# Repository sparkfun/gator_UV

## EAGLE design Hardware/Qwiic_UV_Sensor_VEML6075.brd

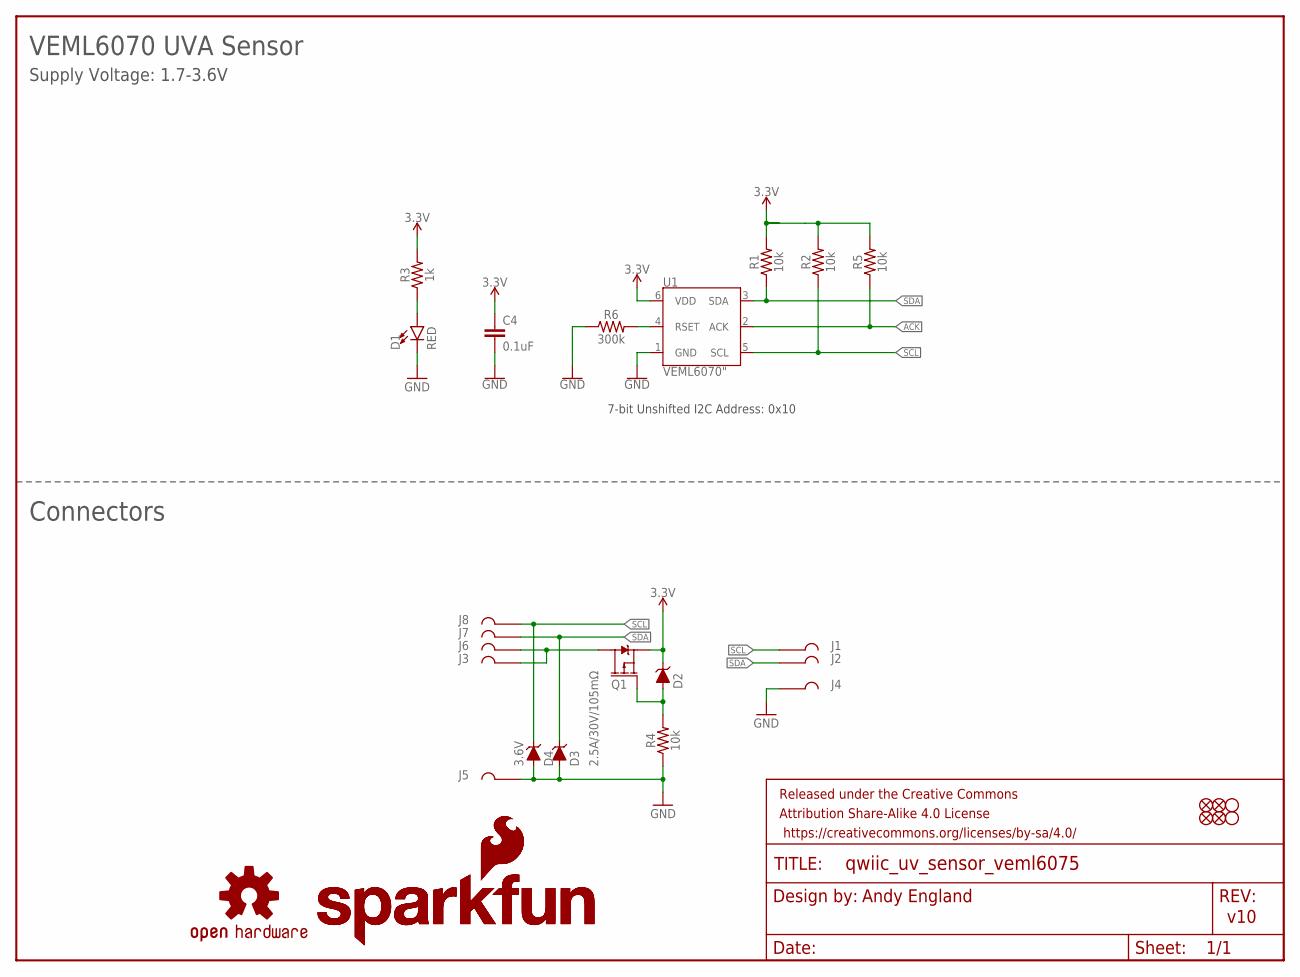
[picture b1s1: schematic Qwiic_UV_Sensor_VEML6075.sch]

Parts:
C4: 0.1uF; 0603
D1: RED; LED-0603
D2, D3, D4: 3.6V; SOD-323
FRAME1: FRAME-LETTER; CREATIVE_COMMONS
J1, J2, J3, J4, J5, J6, J7, J8: GATORGATOR_MINI; GATOR_MINI
JP2, JP5, JP6, JP7: FIDUCIALUFIDUCIAL; MICRO-FIDUCIAL
JP3, JP4: STAND-OFF
LOGO1: OSHW-LOGOMINI; OSHW-LOGO-MINI
Q1: 2.5A/30V/105mΩ; SOT23-3
R1, R2, R4, R5: 10k; 0603
R3: 1k; 0603
R6: 300k; 0603
U1: VEML6070"; VEML6070
U$1, U$2: SFE_LOGO_NAME_FLAME.1_INCH; SFE_LOGO_NAME_FLAME_.1

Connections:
3.3V: C4.1, D2.C, Q1.2 (S), R1.2, R2.2, R3.2, R5.2, U1.6 (VDD)
ACK: R5.1, U1.2 (ACK)
GND: C4.2, D1.C, D3.A, D4.A, J4.P$2, J5.P$2, R4.1, R6.1, U1.1 (GND)
unnamed: J3.P$2, J6.P$2, Q1.3 (D)
unnamed: R6.2, U1.4 (RSET)
unnamed: D1.A, R3.1
unnamed: D2.A, Q1.1 (G), R4.2
SCL: D4.C, J1.P$2, J8.P$2, R2.1, U1.5 (SCL)
SDA: D3.C, J2.P$2, J7.P$2, R1.1, U1.3 (SDA)

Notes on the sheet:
7-bit Unshifted I2C Address: 0x10
v10
VEML6070 UVA Sensor
Connectors
Andy England
Supply Voltage: 1.7-3.6V

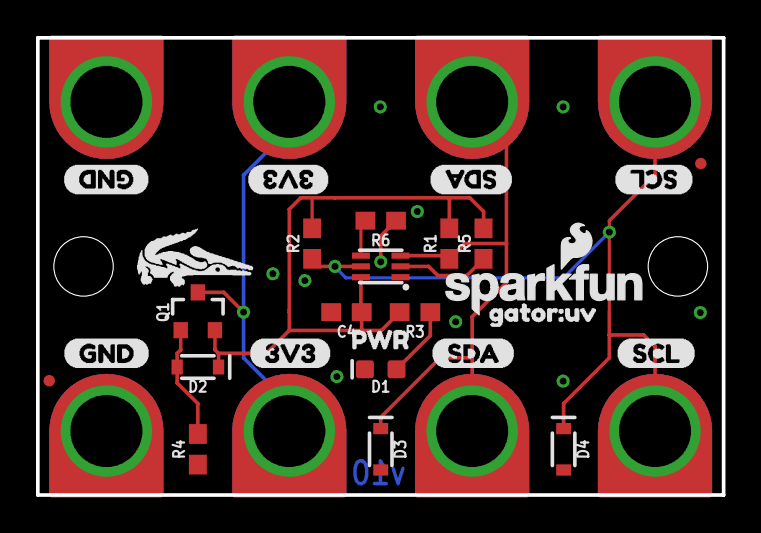
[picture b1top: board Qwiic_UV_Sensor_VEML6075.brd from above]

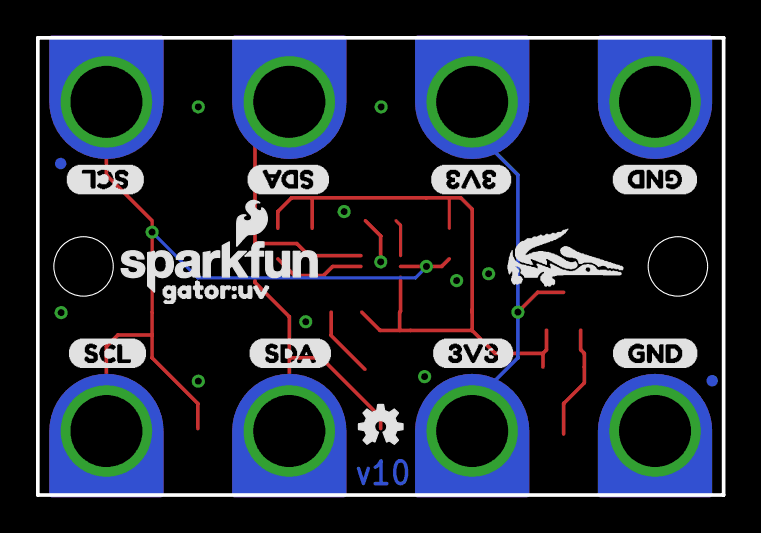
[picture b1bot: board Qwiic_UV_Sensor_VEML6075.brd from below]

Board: 2 copper layers, 38.1 x 25.4 mm, 53 parts (14 on the bottom side), 9 nets.

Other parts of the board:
U$3, U$8, U$14, U$19: 3V33
U$4, U$9, U$13, U$18: GND0
U$5, U$11, U$17, U$21: SCL2
U$6, U$24: GATOR#UV5
U$7, U$12, U$15, U$20: SDA1
U$10: ORDERING_INSTRUCTIONS
U$22, U$23: GATORBIT_FINAL_FOR_SILK#01#PNG
U$25: PWR0

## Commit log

2019-02-25 initial commit, initial layout
2019-02-25 resizing and adding silk
2019-02-27 adding labelling, removing pullup jumper
2019-02-28 adding protection circuitry
2019-02-28 finalizing silk and schematic before design review
2019-03-01 post checklist changes
2019-03-14 updating to VEML6070
2019-03-14 post review changes
2019-04-16 pre design review changes
2019-04-19 engineer run of checklist
2019-04-22 qc double check changes
2019-09-05 removing old prod folder for launch

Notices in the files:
parts and their libraries:
SparkFun-Aesthetics: Licensing: Creative Commons ShareAlike 4.0 International - https://creativecommons.org/licenses/by-sa/4.0
SparkFun-Aesthetics: Released under the Creative Commons Attribution Share-Alike 4.0 License
SparkFun-Aesthetics: https://creativecommons.org/licenses/by-sa/4.0
